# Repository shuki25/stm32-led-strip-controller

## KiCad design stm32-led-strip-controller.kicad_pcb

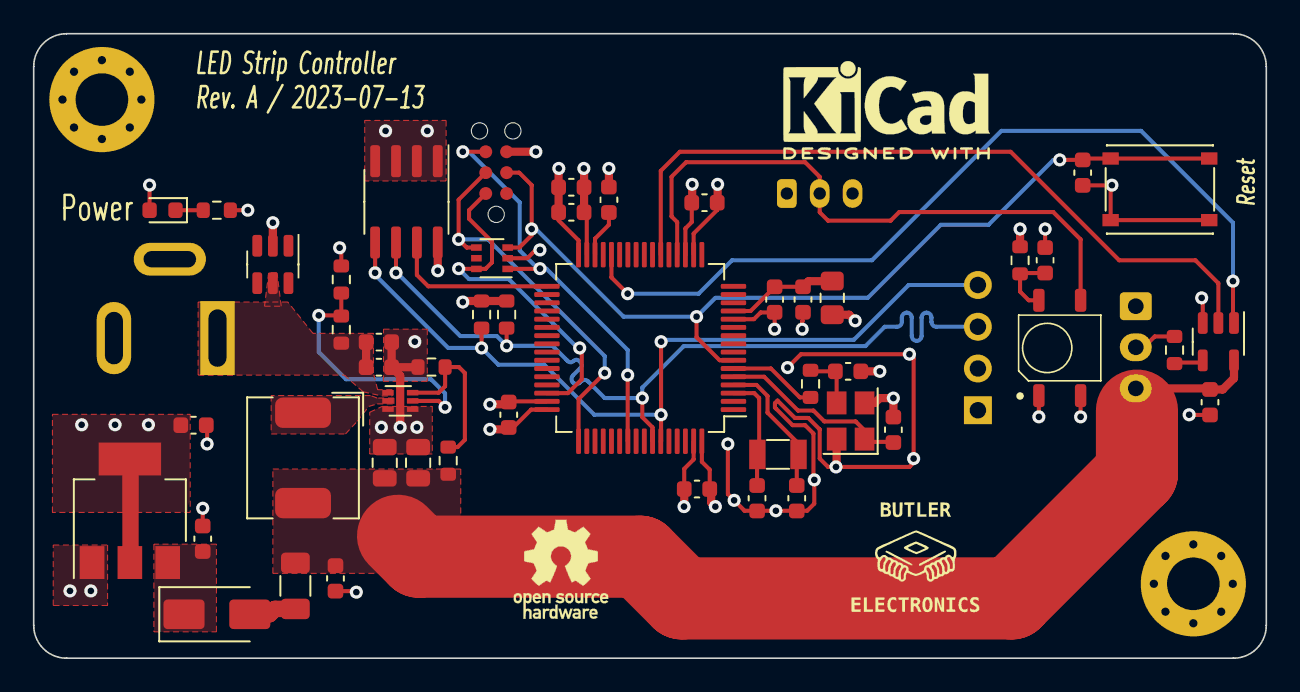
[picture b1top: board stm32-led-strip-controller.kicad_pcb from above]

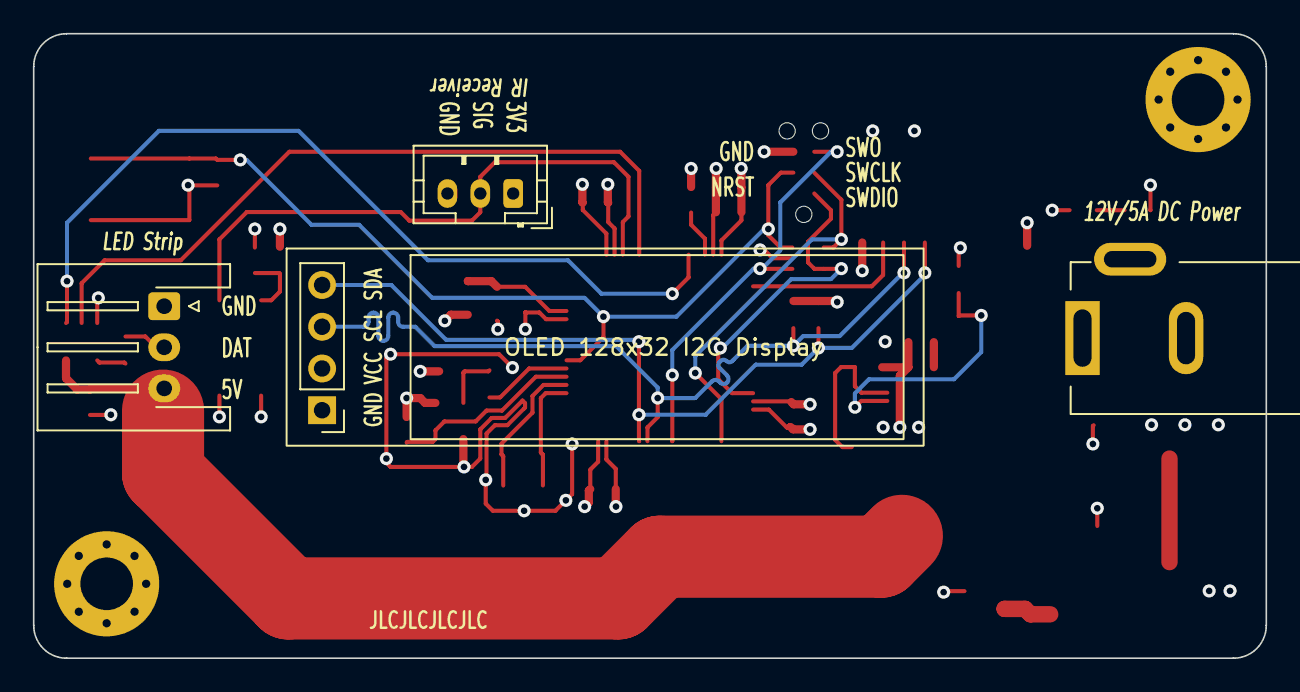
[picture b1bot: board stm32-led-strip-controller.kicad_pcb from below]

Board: 4 copper layers, 75.0 x 38.0 mm, 55 parts (4 on the bottom side), 30 nets.

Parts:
C101, C102, C117: 4.7uF; C_0603_1608Metric
C103, C104, C105, C106, C111, C114, C118, C302, C305: 100nF; C_0603_1608Metric
C107: 1uF; C_0603_1608Metric
C108, C109: 10pF; C_0603_1608Metric
C112, C113: 15pF; C_0603_1608Metric
C201, C202: 22uF; C_0603_1608Metric
C301: 10uF; C_0603_1608Metric
C303, C304: 22uF; C_0805_2012Metric
D102: RED; LED_0603_1608Metric
D103: SS34; D_SMA
D104: SP0505BAJT; SOT-363_SC-70-6
F101: Polyfuse_Small; Fuse_1206_3216Metric
FB101: 600@100MHz; L_0805_2012Metric_Pad1.15x1.40mm_HandSolder
H102, H104: MountingHole; MountingHole_3.2mm_M3_Pad_Via
J101: Tag Connector; TC2030-IDC-NL
J102: Barrel_Jack_Switch; BarrelJack_GCT_DCJ250-10-A-K1-K
J104: JST 2.54 Header; JST_XH_S3B-XH-A-1_1x03_P2.50mm_Horizontal
J106: JST 2.54 Header; JST_PH_B3B-PH-K_1x03_P2.00mm_Vertical
L301: 2.2uH; L_TDK_SPM6530
OLED101: OLED_I2C; OLED_128x32_I2C_4pins
R101: 100; R_0603_1608Metric
R102, R109, R110: 1K5; R_0603_1608Metric
R103: 0; R_0603_1608Metric
R104: 330; R_0603_1608Metric
R301: 100k; R_0603_1608Metric
R302: 226k; R_0603_1608Metric
R303: 15.4k; R_0603_1608Metric
R304: 30k; R_0603_1608Metric
SW106: SW_Push; XKB-Connectivity-TS-1187A-B-A-B
U101: STM32F401RCTx; LQFP-64_10x10mm_P0.5mm
U102: USBLC6-2SC6; SOT-23-6
U103: 74AHCT1G125; SOT-23-5
U104: M24C64-RMN; SOIC-8_3.9x4.9mm_P1.27mm
U105: IRM-H638T/TR2; Everlight_IRM-H638T-TR2
U201: AMS1117-3.3; SOT-223-3_TabPin2
U301: TPS564242DRL; SOT-563
Y101: 16MHz; Crystal_SMD_3225-4Pin_3.2x2.5mm
Y103: 32.768kHz; Crystal_SMD_3215-2Pin_3.2x1.5mm

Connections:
+3.3VA: C106.1, C107.1, FB101.1, U101.13 (VREF+)
+3V3: C102.1, C103.1, C104.1, C105.1, C111.1, C202.2, D102.2 (A), FB101.2, J106.1, OLED101.2 (VCC), R101.2, R109.2, R110.2, U101.19 (VDD), U101.32 (VDD), U101.48 (VDD), U101.64 (VDD), U104.8 (VCC), U201.2 (VO)
+5V: C118.1, C303.1, C304.1, C305.1, F101.1, J104.3, L301.2, R302.1, U103.5 (VCC)
/HSE_IN: C108.1, U101.5 (PH0), Y101.1
/HSE_OUT: R103.1, U101.6 (PH1)
/IR_RECV: J106.2, U101.20 (PA4), U105.3 (OUT)
/LDO_3V3/5V: C201.2, D103.1 (K), U201.3 (VI)
/LSE_IN: C112.2, U101.3 (PC14), Y103.2
/LSE_OUT: C113.2, U101.4 (PC15), Y103.1
/NRST: C114.1, D104.3 (K), J101.3, SW106.1, U101.7 (NRST)
/RGB_LED: U101.22 (PA6), U103.2
/SCL: OLED101.3 (SCL), R110.1, U101.58 (PB6), U104.6 (SCL)
/SDA: OLED101.4 (SDA), R109.1, U101.59 (PB7), U104.5 (SDA)
/SWCLK: D104.4 (K), J101.4, U101.49 (PA14)
/SWDIO: D104.6 (K), J101.2, U101.46 (PA13)
/SWO: D104.1 (K), J101.6, U101.55 (PB3)
/~EEPROM: U101.33 (PB12), U104.7 (~WC)
/~OE: U101.28 (PB2), U103.1
GND: C101.2, C102.2, C103.2, C104.2, C105.2, C106.2, C107.2, C108.2, C109.2, C111.2, C112.1, C113.1, C114.2, C117.2, C118.2, C201.1, C202.1, C301.2, C302.2, C303.2, C304.2, C305.2, D104.2 (A), H102.1, H104.1, J101.5, J102.2, J102.3, J104.1, J106.3, OLED101.1 (GND), R102.2, R303.2, R304.2, SW106.2, U101.12 (VSSA), U101.18 (VSS), U101.31 (VSS), U101.47 (VSS), U101.63 (VSS), U102.2 (GND), U103.3 (GND), U104.1 (E0), U104.2 (E1), U104.3 (E2), U104.4 (VSS), U105.1 (GND), U105.2 (GND), U201.1 (GND), U301.3 (GND), U301.4 (AGND), Y101.2, Y101.4
unnamed: C109.1, R103.2, Y101.3
unnamed: D102.1 (K), R102.1
unnamed: D103.2 (A), F101.2
unnamed: J104.2, R104.1
unnamed: R104.2, U103.4
unnamed: C117.1, U101.30 (VCAP1)
unnamed: C101.1, R101.1, U105.4 (Vs)
unnamed: R301.2, R303.1, U301.5 (EN)
unnamed: R302.2, R304.1, U301.6 (FB)
unnamed: L301.1, U301.2 (SW)
VBUS: C301.1, C302.1, J102.1, R301.1, U102.5 (VBUS), U301.1 (VIN)

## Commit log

2023-07-14 change footprint, remove DIP switch
2023-07-14 update pcb
2023-07-14 remove lock files
